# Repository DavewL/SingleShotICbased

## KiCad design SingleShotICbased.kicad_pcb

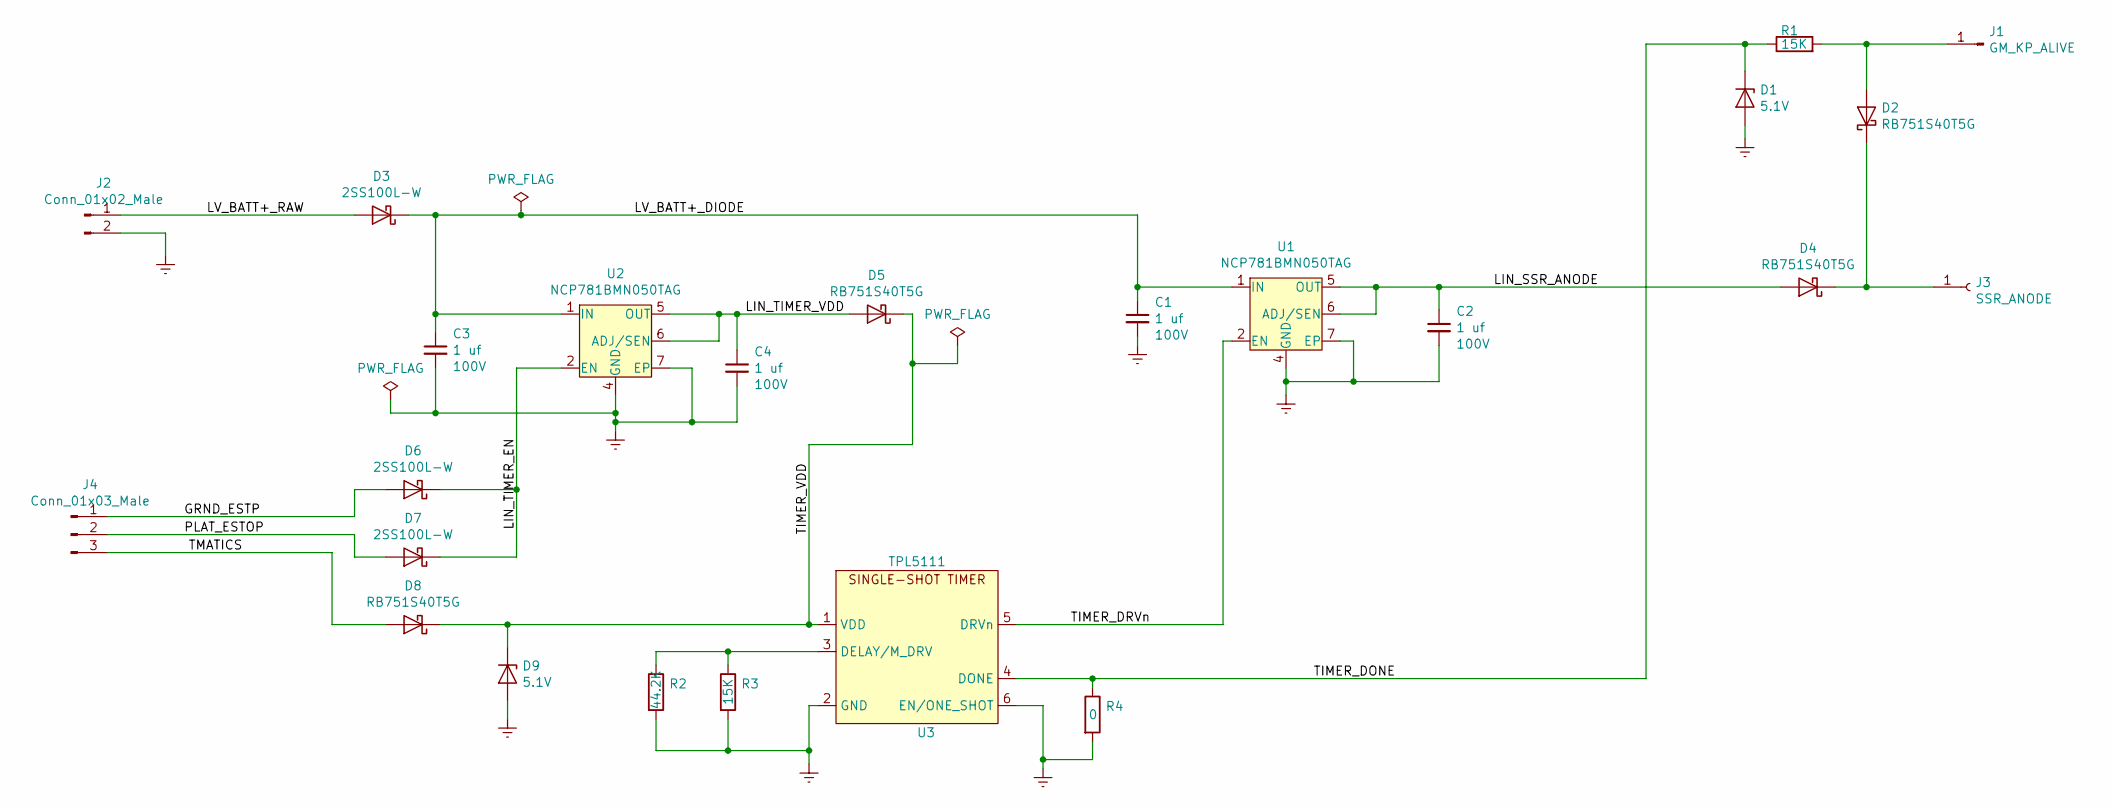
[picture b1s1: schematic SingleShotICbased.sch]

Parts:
C1, C2, C3, C4: 1 uf; C_0805_2012Metric_Pad1.15x1.40mm_HandSolder; VOLTAGE 100V
D1, D9: 5.1V; D_SOD-123
D2, D4, D5, D8: RB751S40T5G; D_SOD-523
D3, D6, D7: 2SS100L-W; D_SOD-123F
J1: GM_KP_ALIVE; PinHeader_1x01_P2.54mm_Horizontal
J2: Conn_01x02_Male; PinHeader_1x02_P2.54mm_Horizontal
J3: SSR_ANODE; PinHeader_1x01_P2.54mm_Horizontal
J4: Conn_01x03_Male; PinHeader_1x03_P2.54mm_Horizontal
R1, R3: 15K; R_0805_2012Metric_Pad1.15x1.40mm_HandSolder
R2: 44.2K; R_0805_2012Metric_Pad1.15x1.40mm_HandSolder
R4: 0; R_0805_2012Metric_Pad1.15x1.40mm_HandSolder
U1, U2: NCP781BMN050TAG; DFN-8-1EP_3x3mm_P0.65mm_EP1.55x2.4mm
U3: TPL5111; SOT-23-6_Handsoldering

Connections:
/GRND_ESTP: D6.2 (A), J4.1
/LIN_SSR_ANODE: C2.1, D4.2 (A), U1.5 (OUT), U1.6 (ADJ/SEN)
/LIN_TIMER_EN: D6.1 (K), D7.1 (K), U2.2 (EN)
/LIN_TIMER_VDD: C4.1, D5.2 (A), U2.5 (OUT), U2.6 (ADJ/SEN)
/LV_BATT+_DIODE: C1.1, C3.1, D3.1 (K), U1.1 (IN), U2.1 (IN)
/LV_BATT+_RAW: D3.2 (A), J2.1
/PLAT_ESTOP: D7.2 (A), J4.2
/TIMER_DONE: D1.1 (K), R1.1, R4.1, U3.4 (DONE)
/TIMER_DRVn: U1.2 (EN), U3.5 (DRVn)
/TIMER_VDD: D5.1 (K), D8.1 (K), D9.1 (K), U3.1 (VDD)
/TMATICS: D8.2 (A), J4.3
Earth: C1.2, C2.2, C3.2, C4.2, D1.2 (A), D9.2 (A), J2.2, R2.2, R3.2, R4.2, U1.4 (GND), U1.7 (EP), U2.4 (GND), U2.7 (EP), U3.2 (GND), U3.6 (EN/ONE_SHOT)
unnamed: D2.1 (K), D4.1 (K), J3.1
unnamed: D2.2 (A), J1.1, R1.2
unnamed: R2.1, R3.1, U3.3 (DELAY/M_DRV)

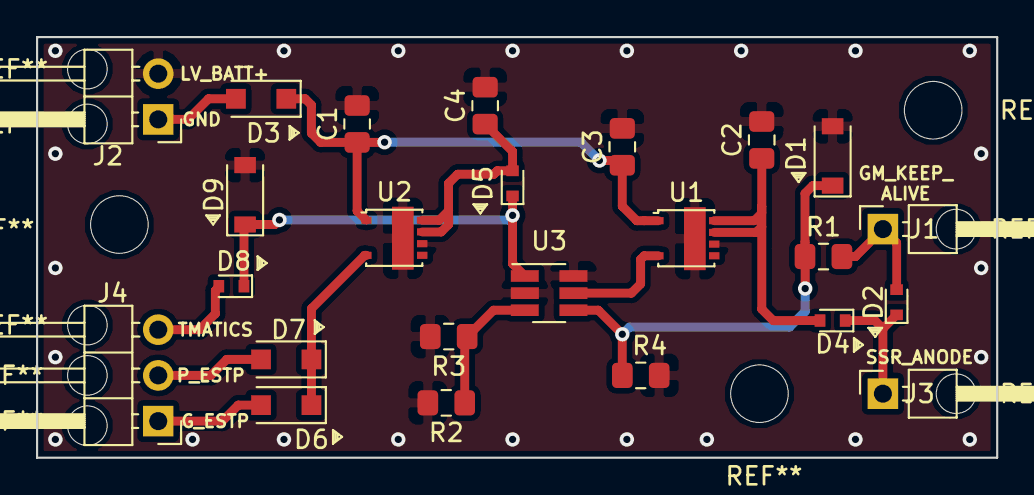
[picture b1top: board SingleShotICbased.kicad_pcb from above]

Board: 2 copper layers, 53.3 x 23.4 mm, 24 parts (0 on the bottom side), 15 nets.

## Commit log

2018-08-23 finished design
2018-09-27 bug fixes and design for enclosure
